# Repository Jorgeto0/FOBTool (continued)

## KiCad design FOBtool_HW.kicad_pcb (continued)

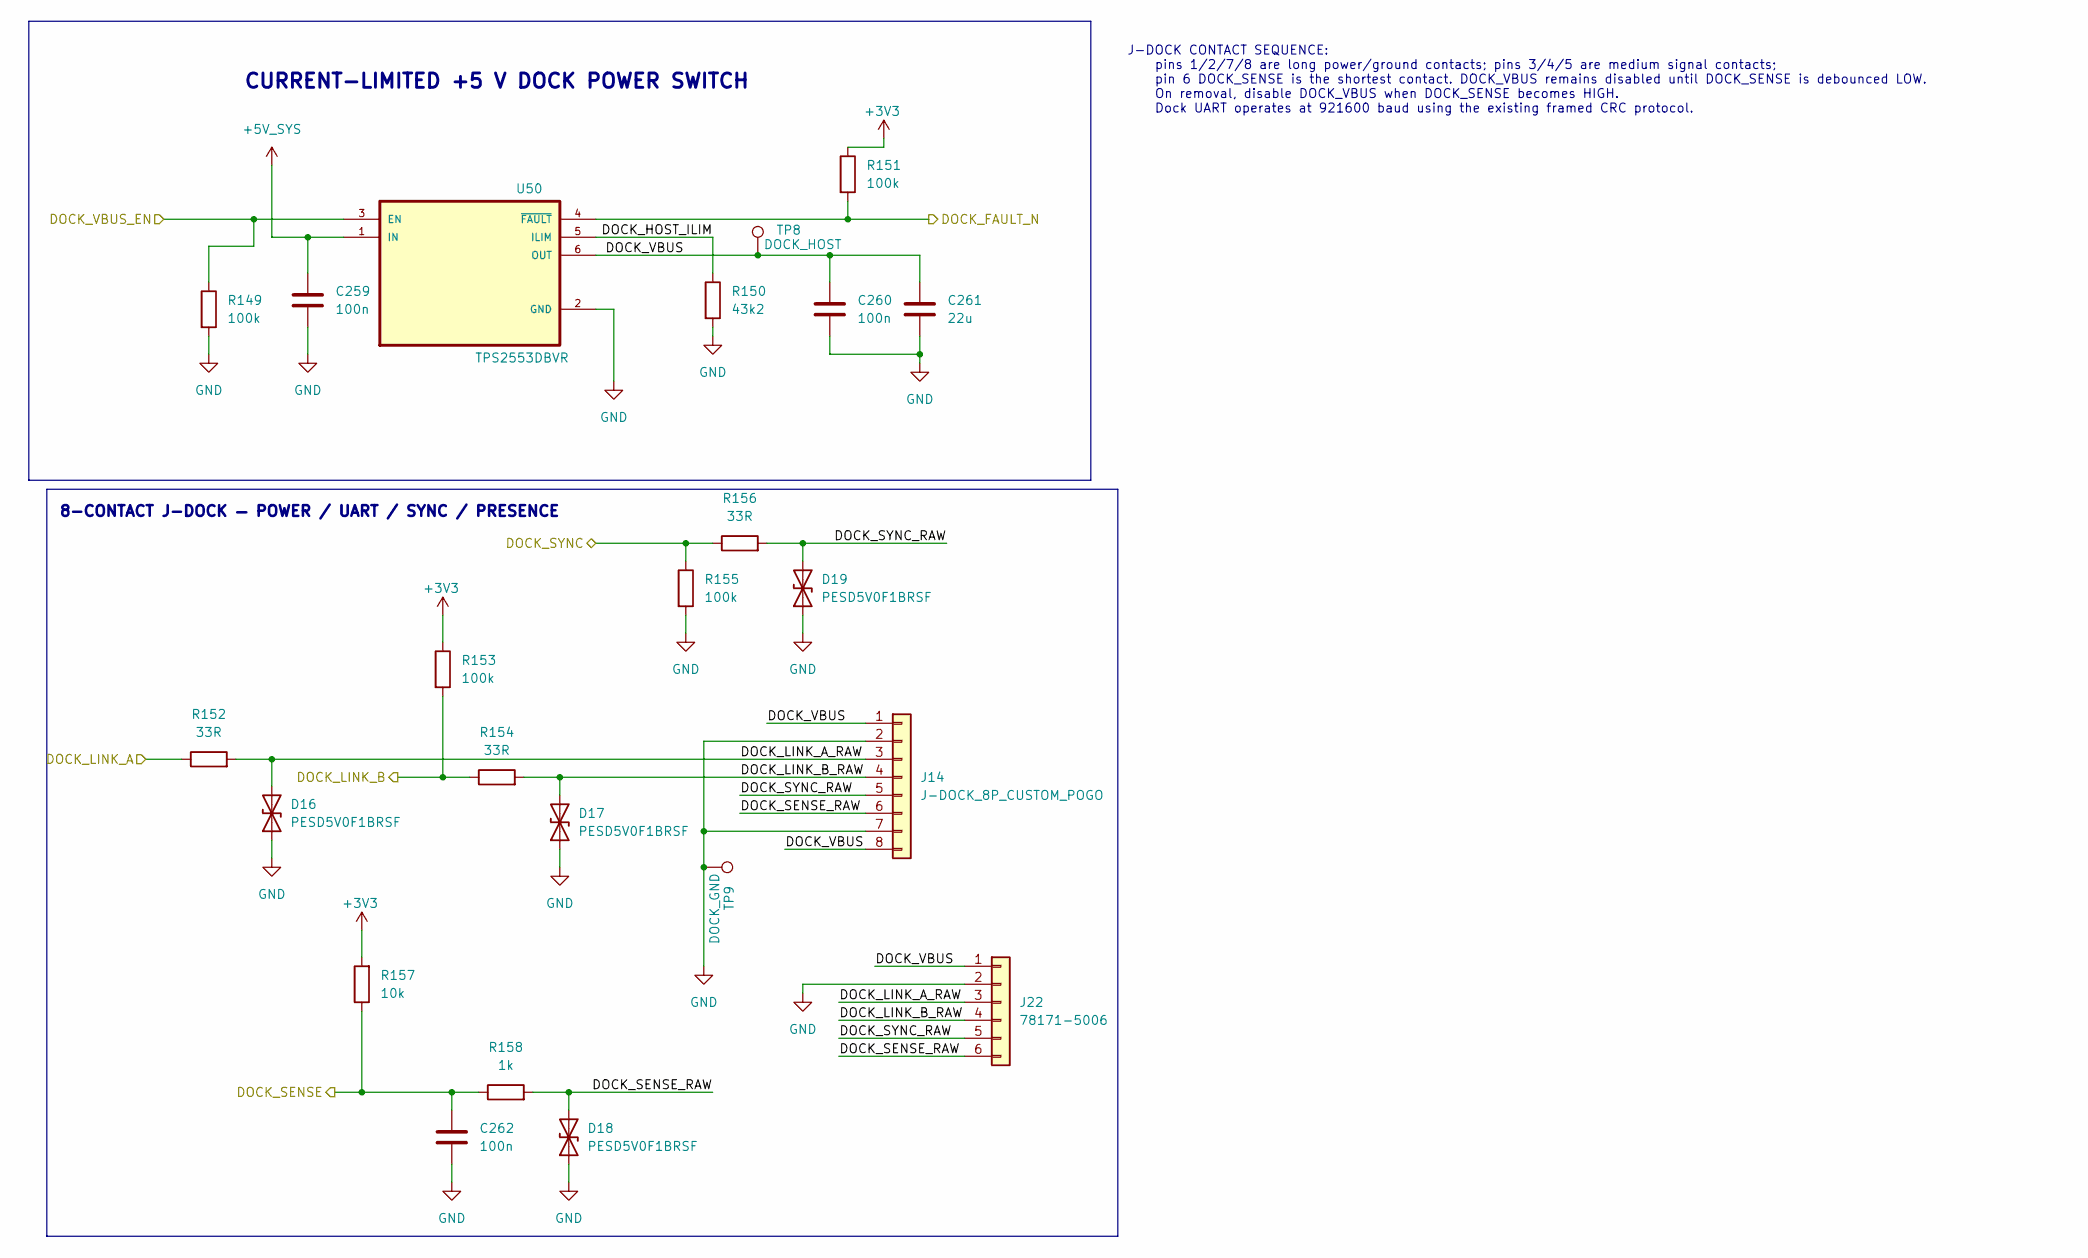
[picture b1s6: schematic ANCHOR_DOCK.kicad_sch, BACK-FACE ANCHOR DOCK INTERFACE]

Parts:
C259, C260, C262: 100n; C_0603_1608Metric; MPN GRM188R71C104KA01D
C261: 22u; C_1206_3216Metric; MPN GRM31CR71A226KE15L
D16, D17, D18, D19: PESD5V0F1BRSF; Nexperia_DSN0603-2_0.6x0.3mm_P0.4mm; MPN PESD5V0F1BRSFYL
J14: J-DOCK_8P_CUSTOM_POGO; MPN N/A
J22: 78171-5006; Molex_78171-5006_1x06_P1.20mm; MPN 78171-5006
R149, R151, R153, R155: 100k; R_0603_1608Metric; MPN RC0603FR-07100KL
R150: 43k2; R_0603_1608Metric; MPN RC0603FR-0743K2L
R152, R154, R156: 33R; R_0603_1608Metric; MPN RC0603FR-0733RL
R157: 10k; R_0603_1608Metric; MPN RC0603FR-0710KL
R158: 1k; R_0603_1608Metric; MPN RC0603FR-071KL
TP8: DOCK_HOST; TestPoint_Pad_D1.5mm; MPN N/A
TP9: DOCK_GND; TestPoint_Pad_D1.5mm; MPN N/A
U50: TPS2553DBVR; SOT95P280X145-6N; MPN TPS2553DBVR

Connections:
+3V3: R151.1, R153.1, R157.2; also elsewhere on the board
+5V_SYS: C259.2, U50.1 (IN); also elsewhere on the board
/ANCHOR_DOCK/DOCK_HOST_ILIM: R150.1, U50.5 (ILIM)
/ANCHOR_DOCK/DOCK_LINK_A_RAW: D16.2 (A2), J14.3, J22.3, R152.2
/ANCHOR_DOCK/DOCK_LINK_B_RAW: D17.2 (A2), J14.4, J22.4, R154.2
/ANCHOR_DOCK/DOCK_SENSE_RAW: D18.2 (A2), J14.6, J22.6, R158.2
/ANCHOR_DOCK/DOCK_SYNC_RAW: D19.2 (A2), J14.5, J22.5, R156.2
/ANCHOR_DOCK/DOCK_VBUS: C260.2, C261.2, J14.1, J14.8, J22.1, TP8.1 (1_1), U50.6 (OUT)
/DOCK_FAULT_N: R151.2, U50.4 (~FAULT); also elsewhere on the board
/DOCK_LINK_A: R152.1; also elsewhere on the board
/DOCK_LINK_B: R153.2, R154.1; also elsewhere on the board
/DOCK_SENSE: C262.2, R157.1, R158.1; also elsewhere on the board
/DOCK_SYNC: R155.1, R156.1; also elsewhere on the board
/DOCK_VBUS_EN: R149.1, U50.3 (EN); also elsewhere on the board
GND: C259.1, C260.1, C261.1, C262.1, D16.1 (A1), D17.1 (A1), D18.1 (A1), D19.1 (A1), J14.2, J14.7, J22.2, R149.2, R150.2, R155.2, TP9.1 (1_1), U50.2 (GND); also elsewhere on the board

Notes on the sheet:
J-DOCK CONTACT SEQUENCE: pins 1/2/7/8 are long power/ground contacts; pins 3/4/5 are medium signal contacts; pin 6 DOCK_SENSE is the shortest contact. DOCK_VBUS remains disabled until DOCK_SENSE is debounced LOW. On removal, disable DOCK_VBUS when DOCK_SENSE becomes HIGH. Dock UART operates at 9216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
8-CONTACT J-DOCK — POWER / UART / SYNC / PRESENCE
CURRENT-LIMITED +5 V DOCK POWER SWITCH

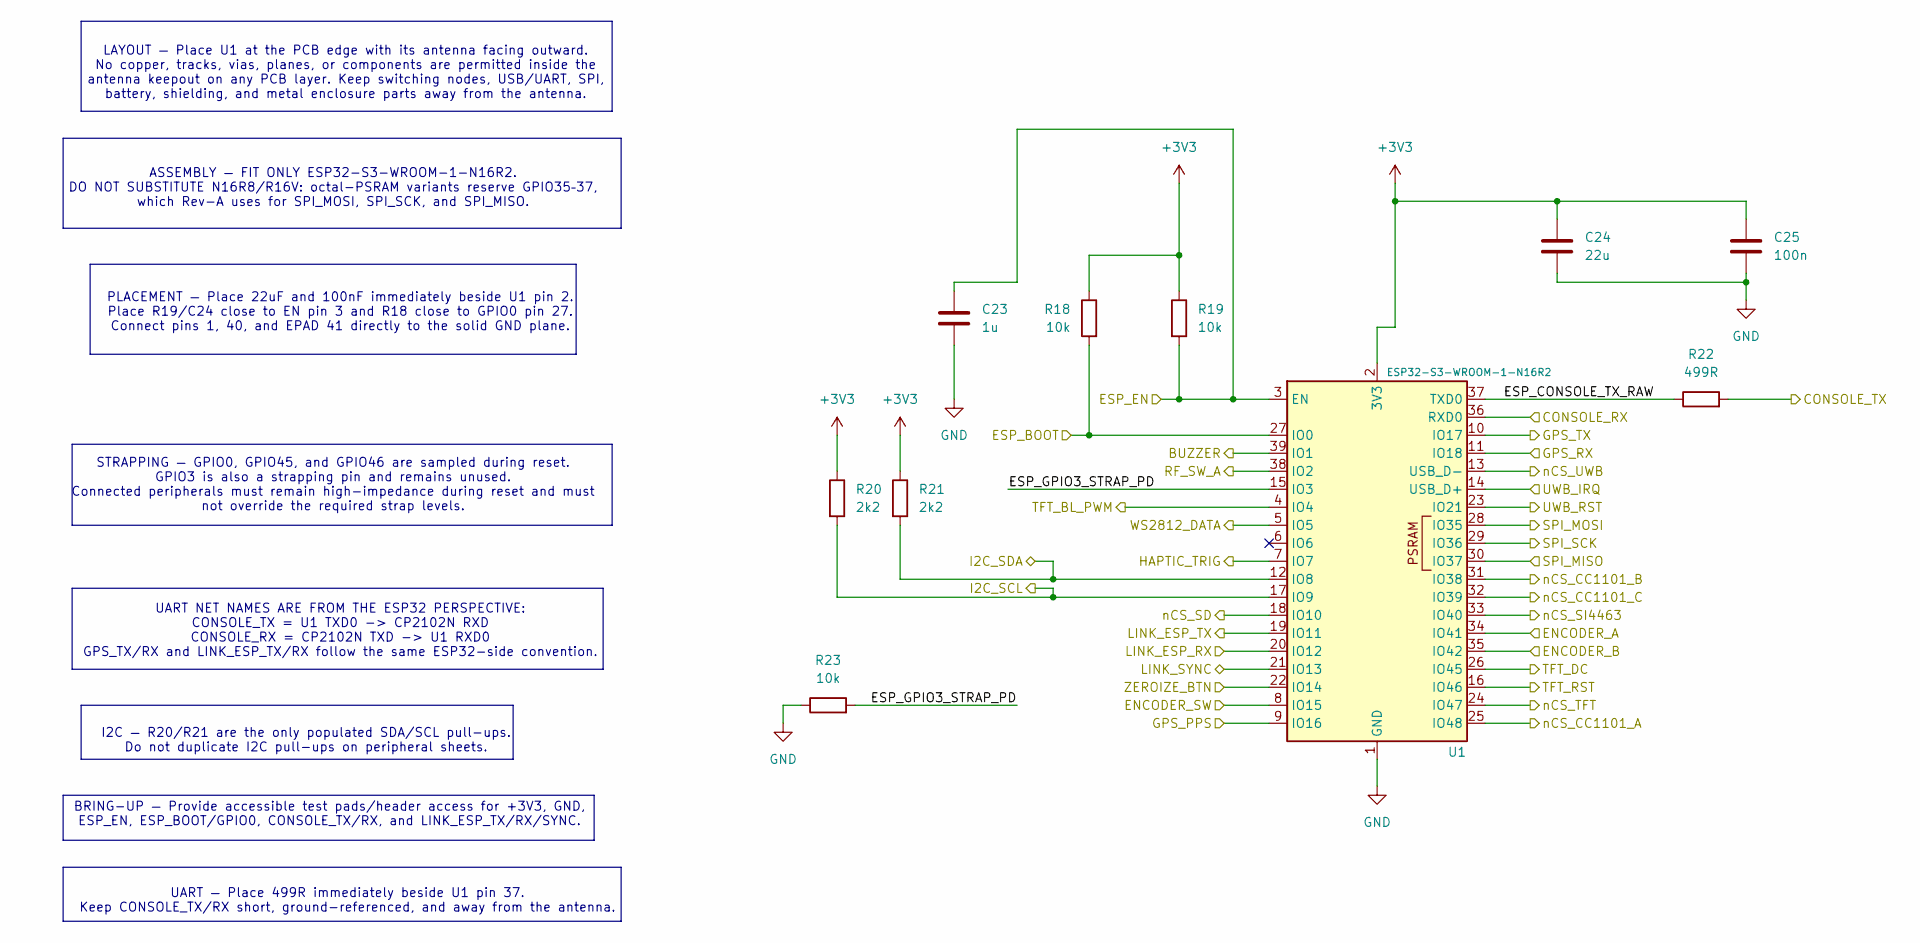
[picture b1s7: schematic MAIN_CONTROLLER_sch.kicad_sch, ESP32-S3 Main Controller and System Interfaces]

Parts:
C23: 1u; C_0603_1608Metric; MPN GRM188R71C105KA12D
C24: 22u; C_1206_3216Metric; MPN GRM31CR71A226KE15L
C25: 100n; C_0603_1608Metric; MPN GRM188R71C104KA01D
R18, R19, R23: 10k; R_0603_1608Metric; MPN RC0603FR-0710KL
R20, R21: 2k2; R_0603_1608Metric; MPN RC0603FR-072K2L
R22: 499R; R_0603_1608Metric; MPN RC0603FR-07499RL
U1: ESP32-S3-WROOM-1-N16R2; ESP32-S3-WROOM-1; MPN ESP32-S3-WROOM-1-N16R2

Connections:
+3V3: C24.1, C25.1, R18.1, R19.1, R20.1, R21.1, U1.2 (3V3); also elsewhere on the board
/BUZZER: U1.39 (IO1); also elsewhere on the board
/CONSOLE_RX: U1.36 (RXD0); also elsewhere on the board
/CONSOLE_TX: R22.2; also elsewhere on the board
/ENCODER_A: U1.34 (IO41); also elsewhere on the board
/ENCODER_B: U1.35 (IO42); also elsewhere on the board
/ENCODER_SW: U1.8 (IO15); also elsewhere on the board
/ESP_BOOT: R18.2, U1.27 (IO0); also elsewhere on the board
/ESP_EN: C23.1, R19.2, U1.3 (EN); also elsewhere on the board
/GPS_PPS: U1.9 (IO16); also elsewhere on the board
/GPS_RX: U1.11 (IO18); also elsewhere on the board
/GPS_TX: U1.10 (IO17); also elsewhere on the board
/HAPTIC_TRIG: U1.7 (IO7); also elsewhere on the board
/I2C_SCL: R20.2, U1.17 (IO9); also elsewhere on the board
/I2C_SDA: R21.2, U1.12 (IO8); also elsewhere on the board
/LINK_ESP_RX: U1.20 (IO12); also elsewhere on the board
/LINK_ESP_TX: U1.19 (IO11); also elsewhere on the board
/LINK_SYNC: U1.21 (IO13); also elsewhere on the board
/MAIN_CONTROLLER/ESP_CONSOLE_TX_RAW: R22.1, U1.37 (TXD0)
/MAIN_CONTROLLER/ESP_GPIO3_STRAP_PD: R23.2, U1.15 (IO3)
/RF_SW_A: U1.38 (IO2); also elsewhere on the board
/SPI_MISO: U1.30 (IO37); also elsewhere on the board
/SPI_MOSI: U1.28 (IO35); also elsewhere on the board
/SPI_SCK: U1.29 (IO36); also elsewhere on the board
/TFT_BL_PWM: U1.4 (IO4); also elsewhere on the board
/TFT_DC: U1.26 (IO45); also elsewhere on the board
/TFT_RST: U1.16 (IO46); also elsewhere on the board
/UWB_IRQ: U1.14 (USB_D+); also elsewhere on the board
/UWB_RST: U1.23 (IO21); also elsewhere on the board
/WS2812_DATA: U1.5 (IO5); also elsewhere on the board
/ZEROIZE_BTN: U1.22 (IO14); also elsewhere on the board
/nCS_CC1101_A: U1.25 (IO48); also elsewhere on the board
/nCS_CC1101_B: U1.31 (IO38); also elsewhere on the board
/nCS_CC1101_C: U1.32 (IO39); also elsewhere on the board
/nCS_SD: U1.18 (IO10); also elsewhere on the board
/nCS_SI4463: U1.33 (IO40); also elsewhere on the board
/nCS_TFT: U1.24 (IO47); also elsewhere on the board
/nCS_UWB: U1.13 (USB_D-); also elsewhere on the board
GND: C23.2, C24.2, C25.2, R23.1, U1.1 (GND), U1.40 (GND), U1.41 (GND); also elsewhere on the board

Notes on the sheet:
I2C — R20/R21 are the only populated SDA/SCL pull-ups. Do not duplicate I2C pull-ups on peripheral sheets.
ASSEMBLY — FIT ONLY ESP32-S3-WROOM-1-N16R2. DO NOT SUBSTITUTE N16R8/R16V: octal-PSRAM variants reserve GPIO35–37, which Rev-A uses for SPI_MOSI, SPI_SCK, and SPI_MISO.
PLACEMENT — Place 22uF and 100nF immediately beside U1 pin 2. Place R19/C24 close to EN pin 3 and R18 close to GPIO0 pin 27. Connect pins 1, 40, and EPAD 41 directly to the solid GND plane.
STRAPPING — GPIO0, GPIO45, and GPIO46 are sampled during reset. GPIO3 is also a strapping pin and remains unused. Connected peripherals must remain high-impedance during reset and must not override the required strap levels.
BRING-UP — Provide accessible test pads/header access for +3V3, GND, ESP_EN, ESP_BOOT/GPIO0, CONSOLE_TX/RX, and LINK_ESP_TX/RX/SYNC.
UART — Place 499R immediately beside U1 pin 37. Keep CONSOLE_TX/RX short, ground-referenced, and away from the antenna.
UART NET NAMES ARE FROM THE ESP32 PERSPECTIVE: CONSOLE_TX = U1 TXD0 -> CP2102N RXD CONSOLE_RX = CP2102N TXD -> U1 RXD0 GPS_TX/RX and LINK_ESP_TX/RX follow the same ESP32-side convention.
LAYOUT — Place U1 at the PCB edge with its antenna facing outward. No copper, tracks, vias, planes, or components are permitted inside the antenna keepout on any PCB layer. Keep switching nodes, USB/UART, SPI, battery, shielding, and metal enclosure parts away from the antenna.

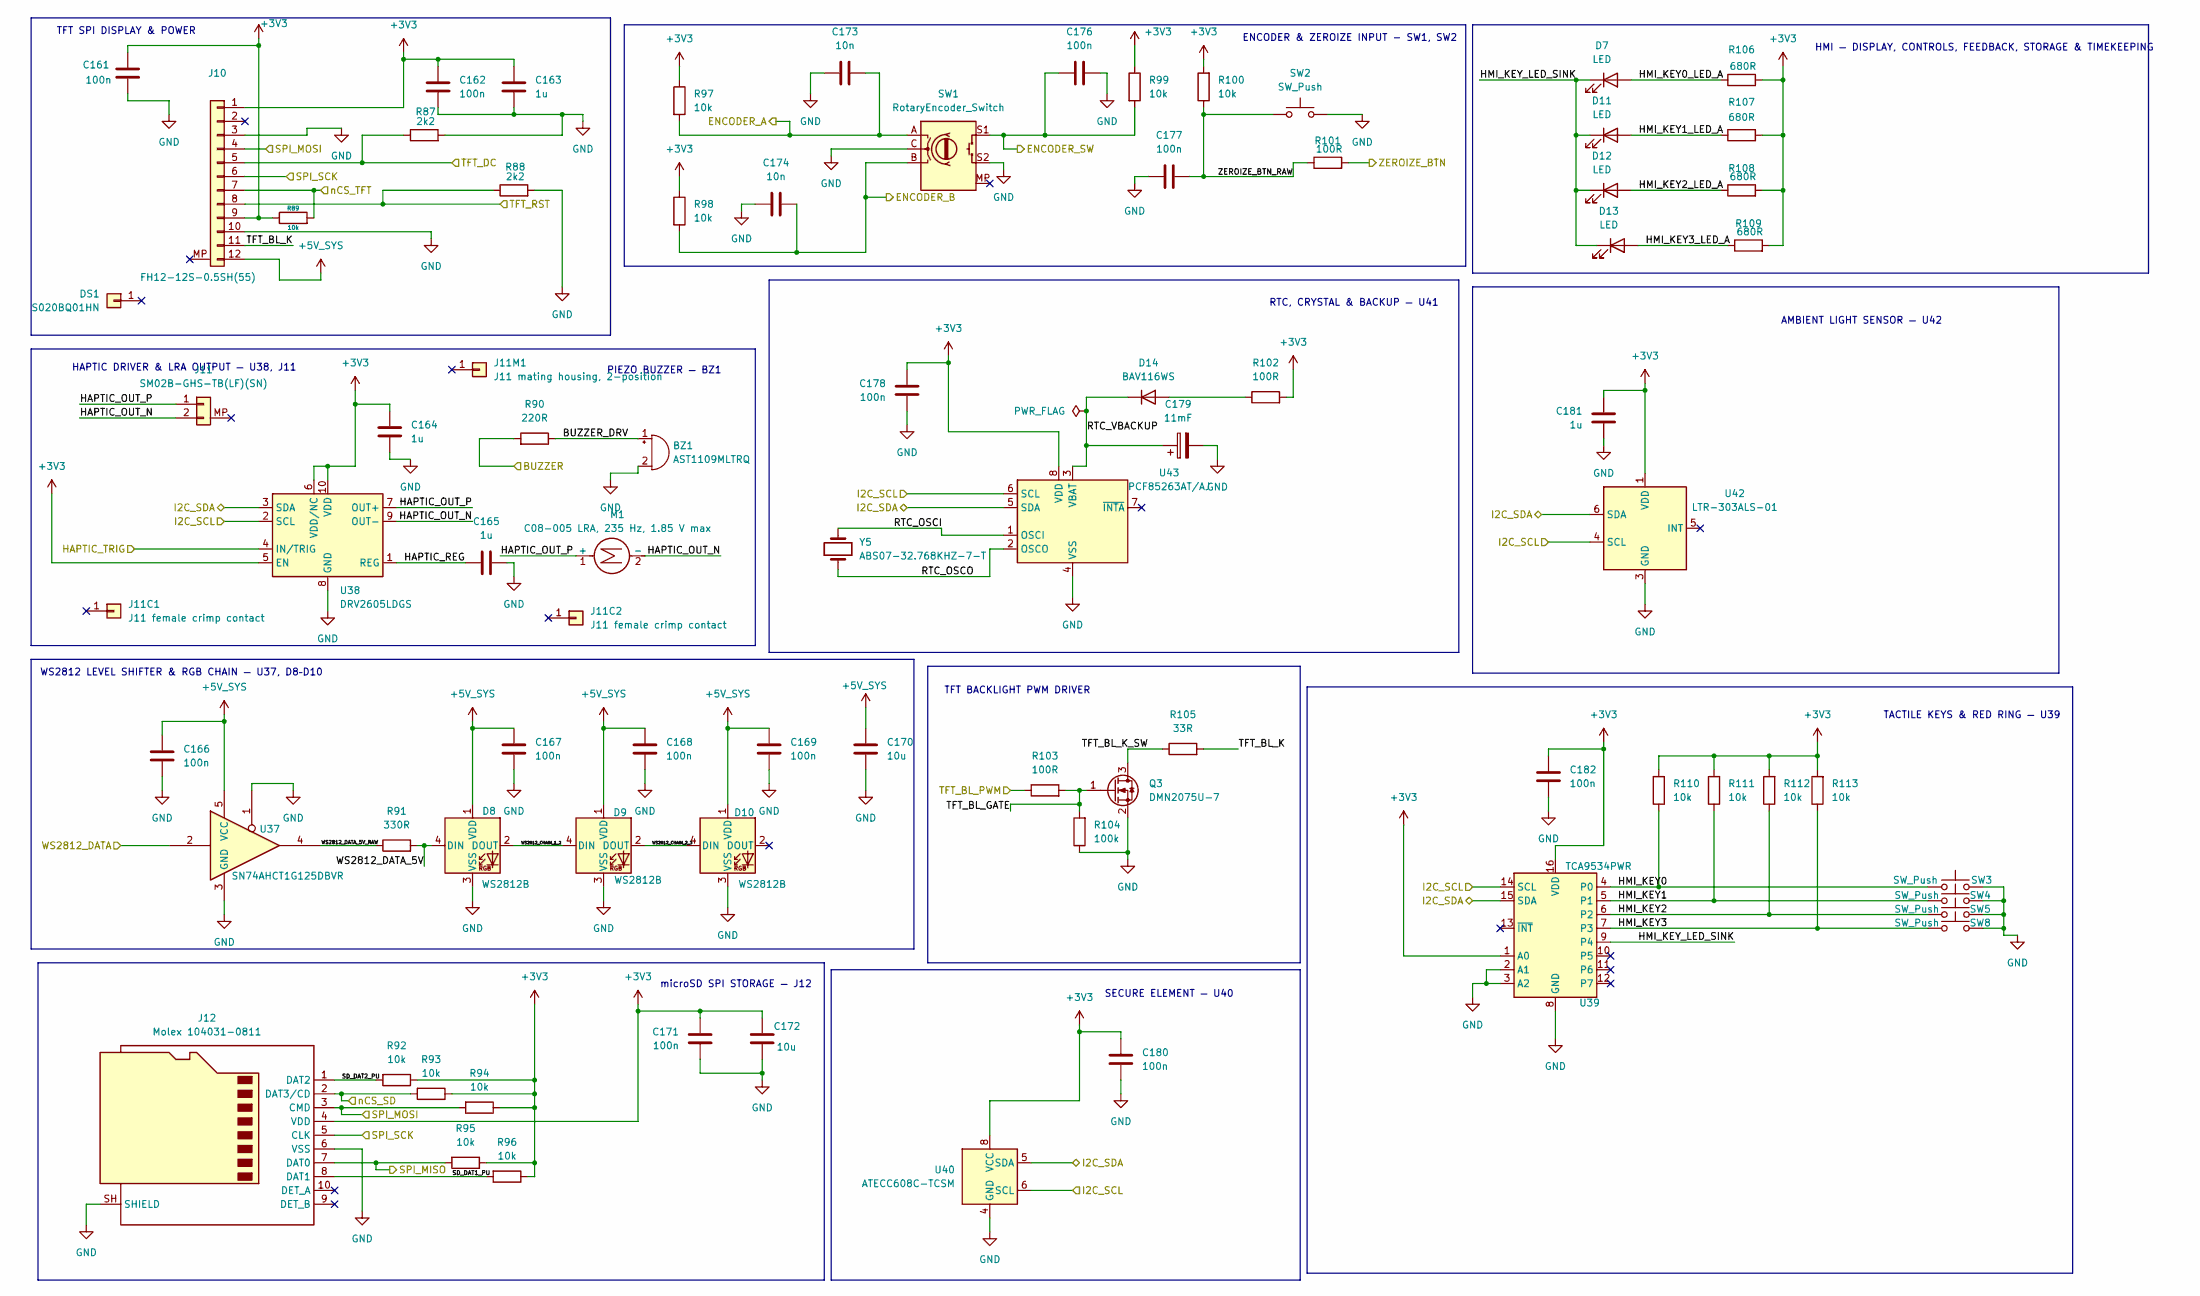
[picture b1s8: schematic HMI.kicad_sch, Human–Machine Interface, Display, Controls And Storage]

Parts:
BZ1: AST1109MLTRQ; Buzzer_Mallory_AST1109MLTRQ; MPN AST1109MLTRQ
C161, C162, C166, C167, C168, C169, C171, C176, C177, C178, C180, C182: 100n; C_0603_1608Metric; MPN GRM188R71C104KA01D
C163, C164, C165, C181: 1u; C_0603_1608Metric; MPN GRM188R71C105KA12D
C170, C172: 10u; C_0805_2012Metric; MPN GRM21BR71A106KE51L
C173, C174: 10n; C_0603_1608Metric; MPN GRM188R71C103KA01D
C179: 11mF; CP_Seiko_CPH3225A_3.2x2.5mm; MPN CPH3225A
D7, D11, D12, D13: LED; LED_0603_1608Metric; MPN LTST-C190KRKT
D8, D9, D10: WS2812B; LED_WS2812B_PLCC4_5.0x5.0mm_P3.2mm; MPN WS2812B-B/W
D14: BAV116WS; D_SOD-323; MPN BAV116WS-7
DS1: S020BQ01HN; MPN S020BQ01HN
J10: FH12-12S-0.5SH(55); Hirose_FH12-12S-0.5SH_1x12-1MP_P0.50mm_Horizontal; MPN FH12-12S-0.5SH(55)
J11: SM02B-GHS-TB(LF)(SN); JST_GH_SM02B-GHS-TB_1x02-1MP_P1.25mm_Horizontal; MPN SM02B-GHS-TB(LF)(SN)
J11C1, J11C2: J11 female crimp contact; MPN SSHL-002T-P0.2
J11M1: J11 mating housing, 2-position; MPN GHR-02V-S
J12: Molex 104031-0811; microSD_HC_Molex_104031-0811; MPN 104031-0811
M1: C08-005 LRA, 235 Hz, 1.85 V max; MPN C08-005
Q3: DMN2075U-7; SOT-23; MPN DMN2075U-7
R87, R88: 2k2; R_0603_1608Metric; MPN RC0603FR-072K2L
R89, R92, R93, R94, R95, R96, R97, R98, R99, R100, R110, R111, R112, R113: 10k; R_0603_1608Metric; MPN RC0603FR-0710KL
R90: 220R; R_0603_1608Metric; MPN RC0603FR-07220RL
R91: 330R; R_0603_1608Metric; MPN RC0603FR-07330RL
R101, R102, R103: 100R; R_0603_1608Metric; MPN RC0603FR-07100RL
R104: 100k; R_0603_1608Metric; MPN RC0603FR-07100KL
R105: 33R; R_1206_3216Metric; MPN ERJ-P08J330V
R106, R107, R108, R109: 680R; R_0603_1608Metric; MPN RC0603FR-07680RL
SW1: RotaryEncoder_Switch; RotaryEncoder_Bourns_PEC11R-4215F-S0024; MPN PEC11R-4215F-S0024
SW2, SW3, SW4, SW5, SW8: SW_Push; SW_SPST_PTS810; MPN PTS810SJM250SMTR LFS
U37: SN74AHCT1G125DBVR; SOT-23-5; MPN SN74AHCT1G125DBVR
U38: DRV2605LDGS; TSSOP-10_3x3mm_P0.5mm; MPN DRV2605LDGSR
U39: TCA9534PWR; TSSOP-16_4.4x5mm_P0.65mm; MPN TCA9534PWR
U40: ATECC608C-TCSM; SOIC-8_3.9x4.9mm_P1.27mm; MPN ATECC608C-TCSMS
U42: LTR-303ALS-01; Lite-On_LTR-303ALS-01; MPN LTR-303ALS-01
U43: PCF85263AT/AJ; SOIC-8_3.9x4.9mm_P1.27mm; MPN PCF85263AT/AJ
Y5: ABS07-32.768KHZ-7-T; Crystal_SMD_3215-2Pin_3.2x1.5mm; MPN ABS07-32.768KHZ-7-T

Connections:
+3V3: C161.1, C162.1, C163.1, C164.1, C171.2, C172.2, C178.2, C180.2, C181.2, C182.2, J10.1, J10.9, J12.4 (VDD), R89.1, R92.1, R93.1, R94.1, R95.1, R96.1, R97.1, R98.1, R99.1, R100.2, R102.2, R106.2, R107.2, R108.2, R109.2, R110.2, R111.2, R112.2, R113.2, U38.5 (EN), U38.6 (VDD/NC), U38.10 (VDD), U39.1 (A0), U39.16 (VDD), U40.8 (VCC), U42.1 (VDD), U43.8 (VDD); also elsewhere on the board
+5V_SYS: C166.1, C167.1, C168.1, C169.1, C170.1, D8.1 (VDD), D9.1 (VDD), D10.1 (VDD), J10.12, U37.5 (VCC); also elsewhere on the board
/BUZZER: R90.2; also elsewhere on the board
/ENCODER_A: C173.2, R97.2, SW1.A; also elsewhere on the board
/ENCODER_B: C174.2, R98.2, SW1.B; also elsewhere on the board
/ENCODER_SW: C176.2, R99.2, SW1.S1; also elsewhere on the board
/HAPTIC_TRIG: U38.4 (IN/TRIG); also elsewhere on the board
/HMI/BUZZER_DRV: BZ1.1 (+), R90.1
/HMI/HAPTIC_OUT_N: J11.2, M1.2 (-), U38.9 (OUT-)
/HMI/HAPTIC_OUT_P: J11.1, M1.1 (+), U38.7 (OUT+)
/HMI/HAPTIC_REG: C165.1, U38.1 (REG)
/HMI/HMI_KEY0: R110.1, SW3.1, U39.4 (P0)
/HMI/HMI_KEY0_LED_A: D7.2 (A), R106.1
/HMI/HMI_KEY1: R111.1, SW4.1, U39.5 (P1)
/HMI/HMI_KEY1_LED_A: D11.2 (A), R107.1
/HMI/HMI_KEY2: R112.1, SW5.1, U39.6 (P2)
/HMI/HMI_KEY2_LED_A: D12.2 (A), R108.1
/HMI/HMI_KEY3: R113.1, SW8.1, U39.7 (P3)
/HMI/HMI_KEY3_LED_A: D13.2 (A), R109.1
/HMI/HMI_KEY_LED_SINK: D7.1 (K), D11.1 (K), D12.1 (K), D13.1 (K), U39.9 (P4)
/HMI/RTC_OSCI: U43.1 (OSCI), Y5.2
/HMI/RTC_OSCO: U43.2 (OSCO), Y5.1
/HMI/RTC_VBACKUP: C179.1, D14.1 (K), U43.3 (VBAT)
/HMI/SD_DAT1_PU: J12.8 (DAT1), R96.2
/HMI/SD_DAT2_PU: J12.1 (DAT2), R92.2
/HMI/TFT_BL_GATE: Q3.1 (G), R103.2, R104.2
/HMI/TFT_BL_K: J10.11, R105.2
/HMI/TFT_BL_K_SW: Q3.3 (D), R105.1
/HMI/WS2812_CHAIN_1_2: D8.2 (DOUT), D9.4 (DIN)
/HMI/WS2812_CHAIN_2_3: D9.2 (DOUT), D10.4 (DIN)
/HMI/WS2812_DATA_5V: D8.4 (DIN), R91.2
/HMI/WS2812_DATA_5V_RAW: R91.1, U37.4
/HMI/ZEROIZE_BTN_RAW: C177.2, R100.1, R101.1, SW2.1
/I2C_SCL: U38.2 (SCL), U39.14 (SCL), U40.6 (SCL), U42.4 (SCL), U43.6 (SCL); also elsewhere on the board
/I2C_SDA: U38.3 (SDA), U39.15 (SDA), U40.5 (SDA), U42.6 (SDA), U43.5 (SDA); also elsewhere on the board
/SPI_MISO: J12.7 (DAT0), R95.2; also elsewhere on the board
/SPI_MOSI: J10.4, J12.3 (CMD), R94.2; also elsewhere on the board
/SPI_SCK: J10.6, J12.5 (CLK); also elsewhere on the board
/TFT_BL_PWM: R103.1; also elsewhere on the board
/TFT_DC: J10.5, R87.1; also elsewhere on the board
/TFT_RST: J10.8, R88.1; also elsewhere on the board
/WS2812_DATA: U37.2; also elsewhere on the board
/ZEROIZE_BTN: R101.2; also elsewhere on the board
/nCS_SD: J12.2 (DAT3/CD), R93.2; also elsewhere on the board
/nCS_TFT: J10.7, R89.2; also elsewhere on the board
GND: BZ1.2 (-), C161.2, C162.2, C163.2, C164.2, C165.2, C166.2, C167.2, C168.2, C169.2, C170.2, C171.1, C172.1, C173.1, C174.1, C176.1, C177.1, C178.1, C179.2, C180.1, C181.1, C182.1, D8.3 (VSS), D9.3 (VSS), D10.3 (VSS), J10.3, J10.10, J12.6 (VSS), J12.SH (SHIELD), Q3.2 (S), R87.2, R88.2, R104.1, SW1.C, SW1.S2, SW2.2, SW3.2, SW4.2, SW5.2, SW8.2, U37.1, U37.3 (GND), U38.8 (GND), U39.2 (A1), U39.3 (A2), U39.8 (GND), U40.4 (GND), U42.3 (GND), U43.4 (VSS); also elsewhere on the board
unnamed: D14.2 (A), R102.1

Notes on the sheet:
TFT BACKLIGHT PWM DRIVER
TFT SPI DISPLAY & POWER
AMBIENT LIGHT SENSOR — U42
RTC, CRYSTAL & BACKUP — U41
SECURE ELEMENT — U40
HAPTIC DRIVER & LRA OUTPUT — U38, J11
PIEZO BUZZER — BZ1
WS2812 LEVEL SHIFTER & RGB CHAIN — U37, D8–D10
HMI — DISPLAY, CONTROLS, FEEDBACK, STORAGE & TIMEKEEPING
TACTILE KEYS & RED RING — U39
ENCODER & ZEROIZE INPUT - SW1, SW2
microSD SPI STORAGE — J12

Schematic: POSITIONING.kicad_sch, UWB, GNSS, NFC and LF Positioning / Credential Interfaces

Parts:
AE1, AE2: UWA.01; Antenna_Taoglas_UWA01_3.2x1.6mm; MPN UWA.01
AE3: Antenna_Loop; MPN N/A
AE4: ADFGP.25E.07.0060A; MPN ADFGP.25E.07.0060A
C183: 220n; C_0402_1005Metric; MPN GRM155R71A224KE01D
C184, C187, C192, C195, C196, C203: 100n; C_0402_1005Metric; MPN GRM155R71C104KA88D
C185, C188, C191: 4n7; C_0402_1005Metric; MPN GRM1555C1H472JE01D
C186, C189, C190, C204: 10u; C_0805_2012Metric; MPN GRM21BR71A106KE51L
C193, C211, C212, C221, C222: 22u; C_1206_3216Metric; MPN GRM31CR71A226KE15L
C194, C197, C199, C201, C202: 2p; C_0402_1005Metric; MPN GJM1555C1H2R0BB01D
C198, C200: NM; C_0402_1005Metric; MPN N/A; not fitted
C205: 10n; C_0603_1608Metric; MPN GRM188R71C103KA01D
C206, C207, C209, C210, C219, C220, C232, C237: 100n; C_0603_1608Metric; MPN GRM188R71C104KA01D
C208, C226, C251, C252: 1n; C_0603_1608Metric; MPN GRM1885C1H102JA01D
C213, C223: 47p; C_0603_1608Metric; MPN GRM1885C1H470JA01D; not fitted
C214, C224: 100p; C_0603_1608Metric; MPN GRM1885C1H101JA01D; not fitted
C215, C225: 220p; C_0603_1608Metric; MPN GRM1885C1H221JA01D; not fitted
C216, C218, C227, C229: 220p; C_0603_1608Metric; MPN GRM1885C1H221JA01D
C217, C228: 3n3; C_0603_1608Metric; MPN GRM1885C1H332JA01D
C230: 1u; C_0603_1608Metric; MPN GRM188R71C105KA12D
C231, C238: 4u7; C_0805_2012Metric; MPN GRM21BR71A475KA73L
C233, C234, C255, C256: 2u2; C_0603_1608Metric; MPN GRM188R71A225KE15D
C235, C236: 12p; C_0603_1608Metric; MPN GRM1885C1H120JA01D; not fitted
C239, C245: 330p; C_0603_1608Metric; MPN GRM1885C1H331JA01D
C240, C242, C244, C246, C248, C250: NM; C_0603_1608Metric; MPN N/A; not fitted
C241, C247: 68p; C_0603_1608Metric; MPN GRM1885C1H680JA01D
C243, C249: 100p; C_0603_1608Metric; MPN GRM1885C1H101JA01D
C253, C254: 15p; C_0603_1608Metric; MPN GRM1885C1H150JA01D
C257, C258: DNP; C_0402_1005Metric; MPN N/A; not fitted
FB8: BLM15PX330SN1D; L_0402_1005Metric; MPN BLM15PX330SN1D
J13: U.FL-R-SMT-1(10); U.FL_Hirose_U.FL-R-SMT-1_Vertical; MPN U.FL-R-SMT-1(10)
J15, J16: S2B-PH-SM4-TB(LF)(SN); JST_PH_S2B-PH-SM4-TB_1x02-1MP_P2.00mm_Horizontal; MPN S2B-PH-SM4-TB(LF)(SN)
J19, J20: PHR-2; MPN PHR-2
J21: 781710002; Molex_Pico-EZmate_78171-0002_1x02-1MP_P1.20mm_Vertical; MPN 781710002
L33: 27n; L_0402_1005Metric; MPN LQG15HS27NJ02D
L34, L35: 160n; L_0603_1608Metric; MPN LQW18ANR16G00D
L38, L39: 422u; MPN CUSTOM-LF-COIL-134K2-REV-A
MP1, MP2, MP3, MP4: SPH-002T-P0.5S; MPN SPH-002T-P0.5S
R114, R115, R116, R117: 0R; R_0603_1608Metric; MPN RC0603JR-070RL
R118: 10R; R_0603_1608Metric; MPN RC0603FR-0710RL
R119, R145, R146, R147, R148: 10k; R_0603_1608Metric; MPN RC0603FR-0710KL
R120, R140: 100k; R_0603_1608Metric; MPN RC0603FR-07100KL
R121, R122, R144: 1k; R_0603_1608Metric; MPN RC0603FR-071KL
R123, R128: 220R; R_0603_1608Metric; MPN RC0603FR-07220RL
R124, R127, R129, R132: 4R7; R_0805_2012Metric; MPN ERJ-P06J4R7V
R125, R130: 150k; R_0603_1608Metric; MPN RC0603FR-07150KL
R126, R131: 47k; R_0603_1608Metric; MPN RC0603FR-0747KL
R133, R134: 2k2; R_0603_1608Metric; MPN RC0603FR-072K2L
R135, R136: 2R7; R_0805_2012Metric; MPN ERJ-P06J2R7V
R137, R138: 6k8; R_0603_1608Metric; MPN RC0603FR-076K8L
R142, R143: 0R; R_0201_0603Metric; MPN ERJ-1GN0R00C
U35: DW3220; QFN-40-1EP_5x5mm_P0.4mm_EP3.6x3.6mm; MPN DW3220TR13
U41: MAX-M10N-10B-00; ublox_MAX-M10N; MPN MAX-M10N-10B-00
U44: PN7160B1HN/C100E; HVQFN-40-1EP_6x6mm_P0.5mm_EP4.1x4.1mm_ThermalVias; MPN PN7160B1HN/C100E
U45, U46: TMS3705FDRQ1; SOIC-16_3.9x9.9mm_P1.27mm; MPN TMS3705FDRQ1
U47: SN74AHCT00PWR; SOP65P640X120-14N; MPN SN74AHCT00PWR
U48: SN74LVC157APWR; TSSOP-16_4.4x5mm_P0.65mm; MPN SN74LVC157APWR
Y7: TXC 8Y38472012; Crystal_SMD_2016-4Pin_2.0x1.6mm; MPN 8Y38472012
Y8: NX2016SA 27.12MHz 10pF; Crystal_SMD_2016-4Pin_2.0x1.6mm; MPN NX2016SA-27.120000MHz-EXS00A-CS06346
Y9, Y10: CSTCR4M00G55B-R0; OSC_CSTCR4M00G55B-R0; PARTREV JGC42-8797

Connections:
+3V3: C184.1, C185.1, C186.1, C187.1, C188.1, C189.1, C193.1, C194.1, C195.1, C203.1, C204.1, C206.1, C230.1, FB8.1, R119.2, R145.1, R148.2, U35.23 (VDD2b), U35.26 (VDD3), U35.29 (VDD1), U41.7 (V_IO), U41.8 (VCC), U44.6 (VDD_PAD), U48.16 (VCC); also elsewhere on the board
+5V_SYS: C207.1, C209.1, C210.1, C211.1, C212.1, C219.1, C220.1, C221.1, C222.1, C231.1, C237.1, C238.1, U44.12 (VBAT2), U44.13 (VDD_UP), U44.28 (VBAT), U45.8 (VDDA), U45.9 (VDD), U45.15 (F_SEL), U46.8 (VDDA), U46.9 (VDD), U46.15 (F_SEL), U47.14 (VCC); also elsewhere on the board
/GPS_PPS: U41.4 (TIMEPULSE); also elsewhere on the board
/GPS_RX: U41.2 (TXD); also elsewhere on the board
/GPS_TX: U41.3 (RXD); also elsewhere on the board
/LF_COIL_SEL: R120.1, U47.4 (2A), U47.5 (2B), U47.13 (4B), U48.1 (~A/B); also elsewhere on the board
/LF_SCIO: U48.4 (1Y); also elsewhere on the board
/LF_TXCT: R119.1, U47.1 (1A), U47.2 (1B); also elsewhere on the board
/NFC_DWL_REQ: R146.1, U44.2 (DWL_REQ); also elsewhere on the board
/NFC_IRQ: U44.8 (IRQ); also elsewhere on the board
/NFC_MISO: U44.5 (SPI_MISO); also elsewhere on the board
/NFC_MOSI: U44.3 (SPI_MOSI); also elsewhere on the board
/NFC_SCK: U44.7 (SPI_SCK); also elsewhere on the board
/NFC_VEN: R147.1, U44.10 (VEN); also elsewhere on the board
/POSITIONING/GNSS_ANT_BIAS_FILT: C205.2, L33.1, R118.2
/POSITIONING/GNSS_RF_IN: J13.1 (In), L33.2, U41.11 (RF_IN)
/POSITIONING/GNSS_VCC_RF: R118.1, U41.14 (VCC_RF)
/POSITIONING/LF_A_DRV: C227.1, J15.1, L38.1, R129.2
/POSITIONING/LF_A_RETURN: C223.2, C224.2, C225.2, C228.2, C229.1, R132.1
/POSITIONING/LF_A_TUNE: C223.1, C224.1, C225.1, C228.1, J15.2, L38.2, R131.1
/POSITIONING/LF_B_DRV: C216.1, J16.1, L39.1, R124.2
/POSITIONING/LF_B_RETURN: C213.2, C214.2, C215.2, C217.2, C218.1, R127.1
/POSITIONING/LF_B_TUNE: C213.1, C214.1, C215.1, C217.1, J16.2, L39.2, R126.1
/POSITIONING/LF_SCIO_A_MUX_IN: R128.1, U48.2 (1A)
/POSITIONING/LF_SCIO_B_MUX_IN: R123.1, U48.3 (1B)
/POSITIONING/LF_SEL_N: U47.6 (2Y), U47.10 (3B)
/POSITIONING/LF_TXCT_N: U47.3 (1Y), U47.9 (3A), U47.12 (4A)
/POSITIONING/NFC_ANT_LOOP_N: AE3.2, J21.2, R136.2
/POSITIONING/NFC_ANT_LOOP_P: AE3.1, J21.1, R135.2
/POSITIONING/NFC_CLK_XTAL1: C254.2, U44.30 (NFC_CLK_XTAL1), Y8.1
/POSITIONING/NFC_FIELD_DET_N: C236.1, U44.24 (ANT2)
/POSITIONING/NFC_FIELD_DET_P: C235.1, U44.23 (ANT1)
/POSITIONING/NFC_MATCH_OUT_N: C236.2, C247.2, C248.2, C249.1, C250.1, R136.1, R138.2
/POSITIONING/NFC_MATCH_OUT_P: C235.2, C241.2, C242.2, C243.1, C244.1, R135.1, R137.2
/POSITIONING/NFC_RXN: C251.2, U44.15 (RXN)
/POSITIONING/NFC_RXP: C252.2, U44.16 (RXP)
/POSITIONING/NFC_RX_MATCH_N: C251.1, R134.1, R138.1
/POSITIONING/NFC_RX_MATCH_P: C252.1, R133.1, R137.1
/POSITIONING/NFC_TX1: L34.1, U44.21 (TX1)
/POSITIONING/NFC_TX1_EMC: C239.1, C240.1, C241.1, C242.1, L34.2, R133.2
/POSITIONING/NFC_TX2: L35.1, U44.19 (TX2)
/POSITIONING/NFC_TX2_EMC: C245.1, C246.1, C247.1, C248.1, L35.2, R134.2
/POSITIONING/NFC_VDD: C255.1, C256.1, U44.26 (VDD_A), U44.27 (VDD), U44.31 (VDD_D)
/POSITIONING/NFC_VDD_IN: C233.1, C234.1, U44.14 (VDD_TX), U44.18 (TVDD_IN), U44.22 (TVDD_IN2)
/POSITIONING/NFC_VDD_VMID: C232.1, U44.17 (VDD_VMID)
/POSITIONING/NFC_XTAL2: C253.2, U44.29 (XTAL2), Y8.3
/POSITIONING/TMS_A_ANT1: R129.1, U45.5 (ANT1)
/POSITIONING/TMS_A_ANT2: R132.2, U45.7 (ANT2)
/POSITIONING/TMS_A_OSC1: U45.11 (OSC1), Y9.1
/POSITIONING/TMS_A_OSC2: U45.10 (OSC2), Y9.3
/POSITIONING/TMS_A_SCIO: R128.2, U45.14 (SCIO)
/POSITIONING/TMS_A_SENSE: R130.1, R131.2, U45.1 (SENSE)
/POSITIONING/TMS_A_SFB: R130.2, U45.2 (SFB)
/POSITIONING/TMS_A_TXCT: C226.1, R121.1, U45.16 (TXCT)
/POSITIONING/TMS_B_ANT1: R124.1, U46.5 (ANT1)
/POSITIONING/TMS_B_ANT2: R127.2, U46.7 (ANT2)
/POSITIONING/TMS_B_OSC1: U46.11 (OSC1), Y10.1
/POSITIONING/TMS_B_OSC2: U46.10 (OSC2), Y10.3
/POSITIONING/TMS_B_SCIO: R123.2, U46.14 (SCIO)
/POSITIONING/TMS_B_SENSE: R125.1, R126.2, U46.1 (SENSE)
/POSITIONING/TMS_B_SFB: R125.2, U46.2 (SFB)
/POSITIONING/TMS_B_TXCT: C208.1, R122.1, U46.16 (TXCT)
/POSITIONING/TXCT_A_RAW: R121.2, U47.8 (3Y)
/POSITIONING/TXCT_B_RAW: R122.2, U47.11 (4Y)
/POSITIONING/UWB_ANT1_FTE: AE1.3 (FTE), R142.2
/POSITIONING/UWB_ANT1_PORT: AE1.1 (RF), C198.1, R114.2, R142.1
/POSITIONING/UWB_ANT2_FTE: AE2.3 (FTE), R143.2
/POSITIONING/UWB_ANT2_PORT: AE2.1 (RF), C200.1, R115.2, R143.1
/POSITIONING/UWB_RF1_IC: C197.1, U35.18 (RF1)
/POSITIONING/UWB_RF1_MATCH: C197.2, C257.1, R114.1
/POSITIONING/UWB_RF2_IC: C199.1, U35.13 (RF2)
/POSITIONING/UWB_RF2_MATCH: C199.2, C258.1, R115.1
/POSITIONING/UWB_RST_IC: R144.1, U35.33 (~RST)
/POSITIONING/UWB_VDD2A: C190.1, C191.1, C192.1, FB8.2, U35.28 (VDD2a)
/POSITIONING/UWB_VIO_D: C196.1, U35.38 (VIO_D)
/POSITIONING/UWB_VTX_D: C183.1, U35.27 (VTX_D)
/POSITIONING/UWB_XTI_IC: R116.1, U35.21 (XTI)
/POSITIONING/UWB_XTI_XTAL: C201.1, R116.2, Y7.3
/POSITIONING/UWB_XTO_IC: R117.1, U35.22 (XTO)
/POSITIONING/UWB_XTO_XTAL: C202.1, R117.2, Y7.1
/SPI_MISO: U35.36 (SPIMISO); also elsewhere on the board
/SPI_MOSI: U35.35 (SPIMOSI); also elsewhere on the board
/SPI_SCK: U35.34 (SPICLK); also elsewhere on the board
/UWB_IRQ: R140.2, U35.1 (IRQ); also elsewhere on the board
/UWB_RST: R144.2; also elsewhere on the board
/nCS_NFC: R145.2, U44.1 (SPI_NSS); also elsewhere on the board
/nCS_UWB: R148.1, U35.37 (~SPICS); also elsewhere on the board
GND: C183.2, C184.2, C185.2, C186.2, C187.2, C188.2, C189.2, C190.2, C191.2, C192.2, C193.2, C194.2, C195.2, C196.2, C198.2, C200.2, C201.2, C202.2, C203.2, C204.2, C205.1, C206.2, C207.2, C208.2, C209.2, C210.2, C211.2, C212.2, C216.2, C218.2, C219.2, C220.2, C221.2, C222.2, C226.2, C227.2, C229.2, C230.2, C231.2, C232.2, C233.2, C234.2, C237.2, C238.2, C239.2, C240.2, C243.2, C244.2, C245.2, C246.2, C249.2, C250.2, C253.1, C254.1, C255.2, C256.2, C257.2, C258.2, J13.2 (Ext), R120.2, R140.1, R146.2, R147.2, U35.10 (GND), U35.11 (GND), U35.12 (GND), U35.14 (GND), U35.15 (GND), U35.16 (GND), U35.17 (GND), U35.19 (GND), U35.20 (GND), U35.24 (VSS2), U35.25 (VSS3), U35.30 (VSS1), U35.32 (WAKEUP), U35.39 (VSS), U35.40 (VSS), U35.41 (EP), U41.1 (GND), U41.10 (GND), U41.12 (GND), U44.4 (GND), U44.9 (GND), U44.20 (GND), U44.41 (GND), U45.6 (VSSA), U45.12 (VSSB), U46.6 (VSSA), U46.12 (VSSB), U47.7 (GND), U48.5 (2A), U48.6 (2B), U48.8 (GND), U48.10 (3B), U48.11 (3A), U48.13 (4B), U48.14 (4A), U48.15 (~G), Y7.2 (G), Y7.4 (G), Y8.2 (G), Y8.4 (G), Y9.2, Y10.2; also elsewhere on the board

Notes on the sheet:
LF HDX 134.2 kHz – Dual Orthogonal Coil Front Ends
LF HDX 134.2 kHz — COIL A
OFF-BOARD 134.2 kHz ORTHOGONAL LF COILS
NFC CONTROLLER, MATCHING, FIELD DETECTOR AND LOOP ANTENNA
LF COIL SELECT, TXCT GATING AND SCIO MUX
GNSS RECEIVER, ACTIVE-ANTENNA BIAS AND SMA
External rear NFC antenna assembly—geometry and tuning pending
UWB TRANSCEIVER, CLOCK, DUAL ANTENNAS AND SPI
LF HDX 134.2 kHz — COIL B
UWB PDoA ANTENNA LAYOUT: Place AE1 and AE2 on the same PCB edge with identical orientation. Follow the Taoglas UWA.01 land pattern and maintain its 7.5 × 6.0 mm all-layer copper keepout for each antenna. Route RF1 and RF2 as phase-matched 50 Ω traces with identical transitions and grounding. Target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

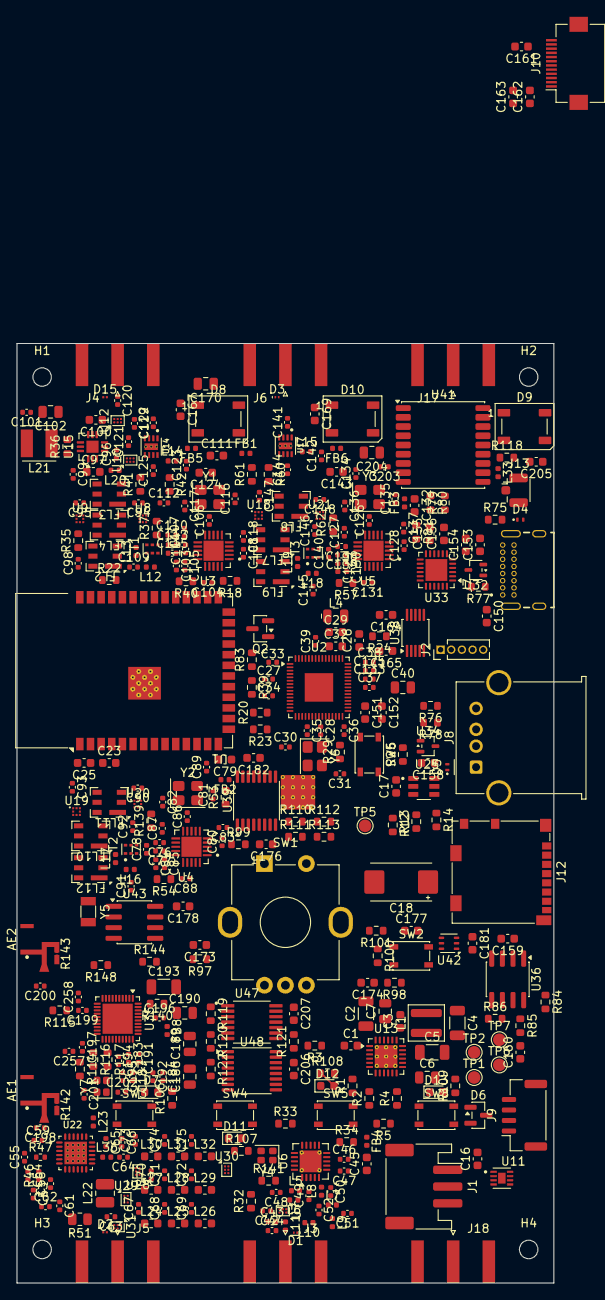
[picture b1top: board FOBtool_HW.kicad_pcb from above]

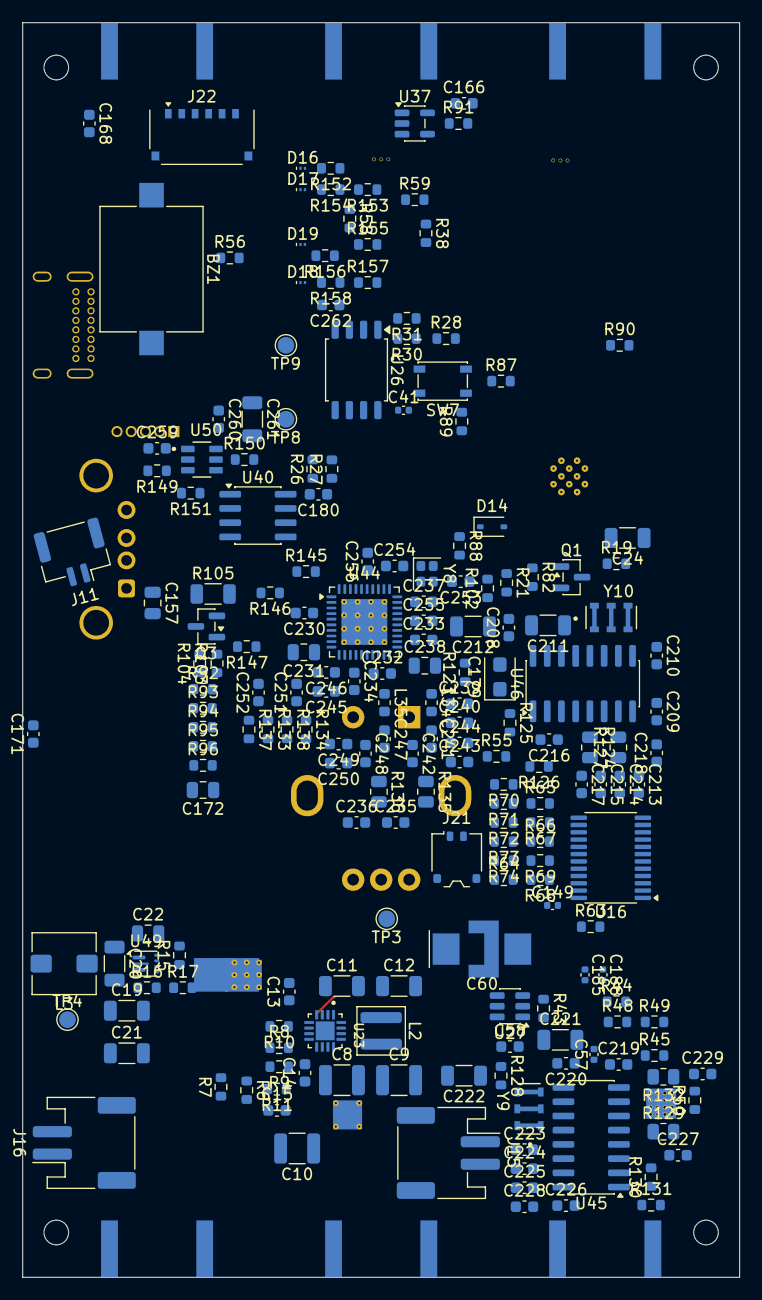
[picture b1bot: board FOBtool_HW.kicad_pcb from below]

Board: 6 copper layers, 64.0 x 112.0 mm, 599 parts (200 on the bottom side), 360 nets.
